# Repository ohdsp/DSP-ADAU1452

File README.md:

# [Open Hardware DSP Platform](http://www.ohdsp.org)
## ADAU145x DSP supporting ADAU1452, ADAU1451, and ADAU1450 devices
### Revision 2.1 - KiCad 9.0.4 update only - No Schematic/PCB changes
###### DSP-ADAU1452
---
# README
### Disclaimer
Copyright Paul Janicki 2025

Licensed under the TAPR Open Hardware License (www.tapr.org/OHL)

This documentation is distributed WITHOUT ANY EXPRESS OR IMPLIED WARRANTY, INCLUDING OF MERCHANTABILITY, SATISFACTORY QUALITY AND FITNESS FOR A PARTICULAR PURPOSE.

### What is this repository for?

**Quick summary**

This is a simple self-bootable ADAU1450, ADAU1451, or ADAU1452 based DSP board with 4 I2S (TDM/left and right justified and more) input and 4 output connectors. When used with the ADAU1451 and ADAU1452 parts there are also optical and coaxial SPDIF input and output connectors. 

There is an I2C/SPI connector for connection to the Analog Devices SigmaStudio USBi to EZ-Board Adapter (ADZS-USBI2EZB) or anything that will do the same job (eg freeUSBi). The board also features master and slave SPI connectors for use with other OHDSP boards. The board has space for a self-boot EEPROM and so with the ADZS-USBI2EZB or compatible device the board can be programmed as you wish and will selfboot the last program written when enabled. 

This board forms the core of the open hardware DSP platform which is designed to be a highly customisable and flexible DSP platform. 

This repository contains the KiCad design files, manufacturing Gerber/drill files, and PDF/drawing files for this board.

### What is the project folder structure?
Most folder names are self explanatory. Starting from the top level: \
*DSP-ADAU1452*
+ *Bill of Materials*  - This contains the bill of materials in CVS, LibreOffice Calc and XML formats
+ *Drawings*
    + *PCB* - This contains SVG and PDF outputs of PCB copper layers and assembly drawings
    + *Schematics* - This contains the PDF schematic drawing
+ *Gerbers* - This contains the PCB Gerbers and drill drawings for manufacture, there is also a zip file ready to send to most manufacturers
+ *KiCad* - This contains the original KiCad schematic and PCB design files

### How do I get set up?

**Summary of set up**

1. Set your self up a directory on a local disk, something simple will make life easier (eg C:\Electronics on Windows as used here), but anywhere will do just fine.
2. Download the Kicad-Libs from [https://github.com/ohdsp/KiCad-Libs](https://github.com/ohdsp/KiCad-Libs) and place in C:\Electronics\Kicad-Libs (or your chosen folder) 
3. Create a OHDSP subdirectory in C:\Electronics (so C:\Electronics\OHDSP)
3. Download this project to C:\Electronics\OHDSP\DSP-ADAU1452
4. Fire up Kicad
5. Open the main project file C:\Electronics\OHDSP\DSP-ADAU1452\KiCad\DSP-ADAU1452.pro
6. (Optional) Setup Pcbnew component library as below.
7. Do as you wish with the project, just keep it under the TAPR Open Hardware License.

Make sure your git setup doesn't exclude files used in the project (like .LIB files) or things may go wrong down the line.

**KiCad Library Configuration**

Note that you need to setup a Pcbnew library, but the eeschema libraries should work without any changes if you followed the instructions above.

To setup Pcbnew libraries:

In Pcbnew go to Preferences -> Footprint Libraries Manager. Under Global Libraries tab in the top list check if there is a nickname "MyKiCadLibs-Footprints" (usually at the end of the list). If there is but it points to the wrong place then change the Library Path to point to MyKiCadLibs-Footprints (eg C:\Electronics\KiCad-Libs\MyKiCadLibs-Footprints.pretty) folder for your setup. If this is missing you can use "Append with Wizard", choose "Files on my computer", click next, browse to library location (eg C:\Electronics\KiCad-Libs\MyKiCadLibs-Footprints.pretty) and select the folder MyKiCadLibs-Footprints.pretty, click next, check the Status column states OK and the Format is KiCad (if not re-download the library) and click next, then select "To global library configuration..." and click Finish.

To setup eeschema component libraries:
Either from KiCad project window go to Tools -> Run Library Editor OR under eeschema, go to Tools -> Library Editor. Then Preferences -> Component Libraries.

The top section "Component Library Files" should ideally contain only two libraries, the "power" library that ships with KiCad and "MyKiCadLibs-Lib" available from above. To setup MyKiCadLibs-Lib as a relative path under the "User defined search path" click add. Browse to the location of KiCad-Libs you download above (eg C:\Electronics\KiCad-Libs) and click "Select Folder". Say yes to add a relative path. Under component library files click add, browse to the KiCad-libs again (eg C:\Electronics\KiCad-Libs), select file "MyKiCadLibs-Lib.lib" and click open. MyKiCadLibs-lib should appear in the component library list with no path as it will be using the user defined search path set in the box below.

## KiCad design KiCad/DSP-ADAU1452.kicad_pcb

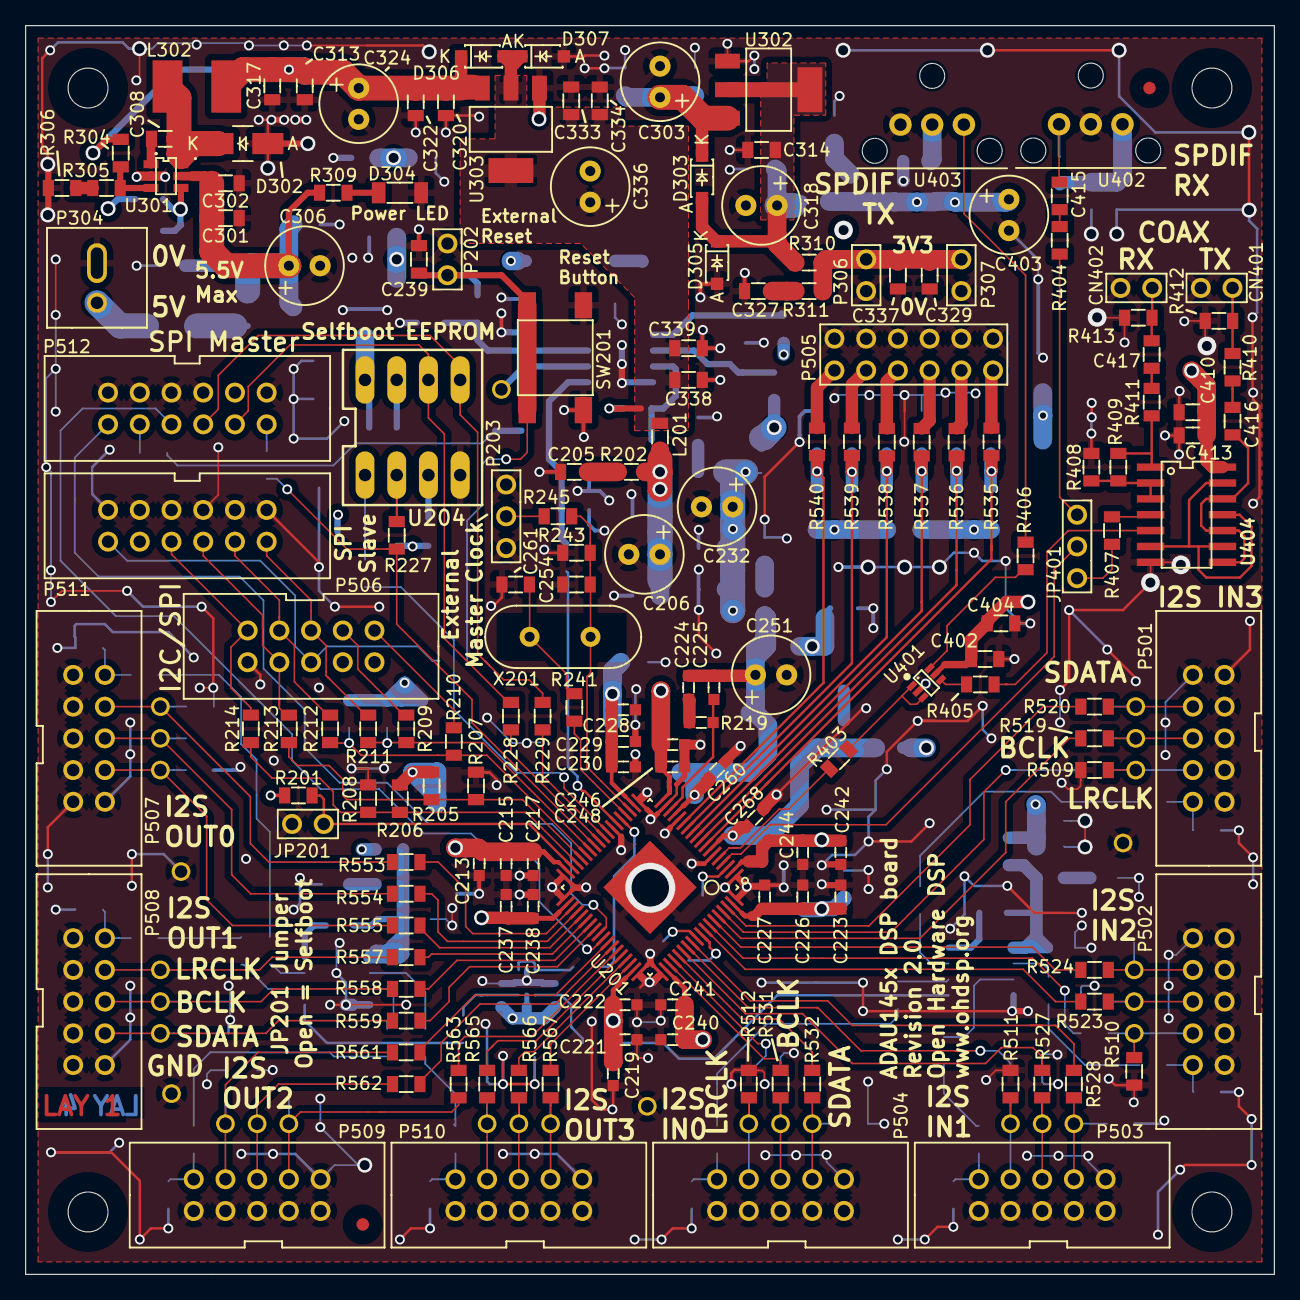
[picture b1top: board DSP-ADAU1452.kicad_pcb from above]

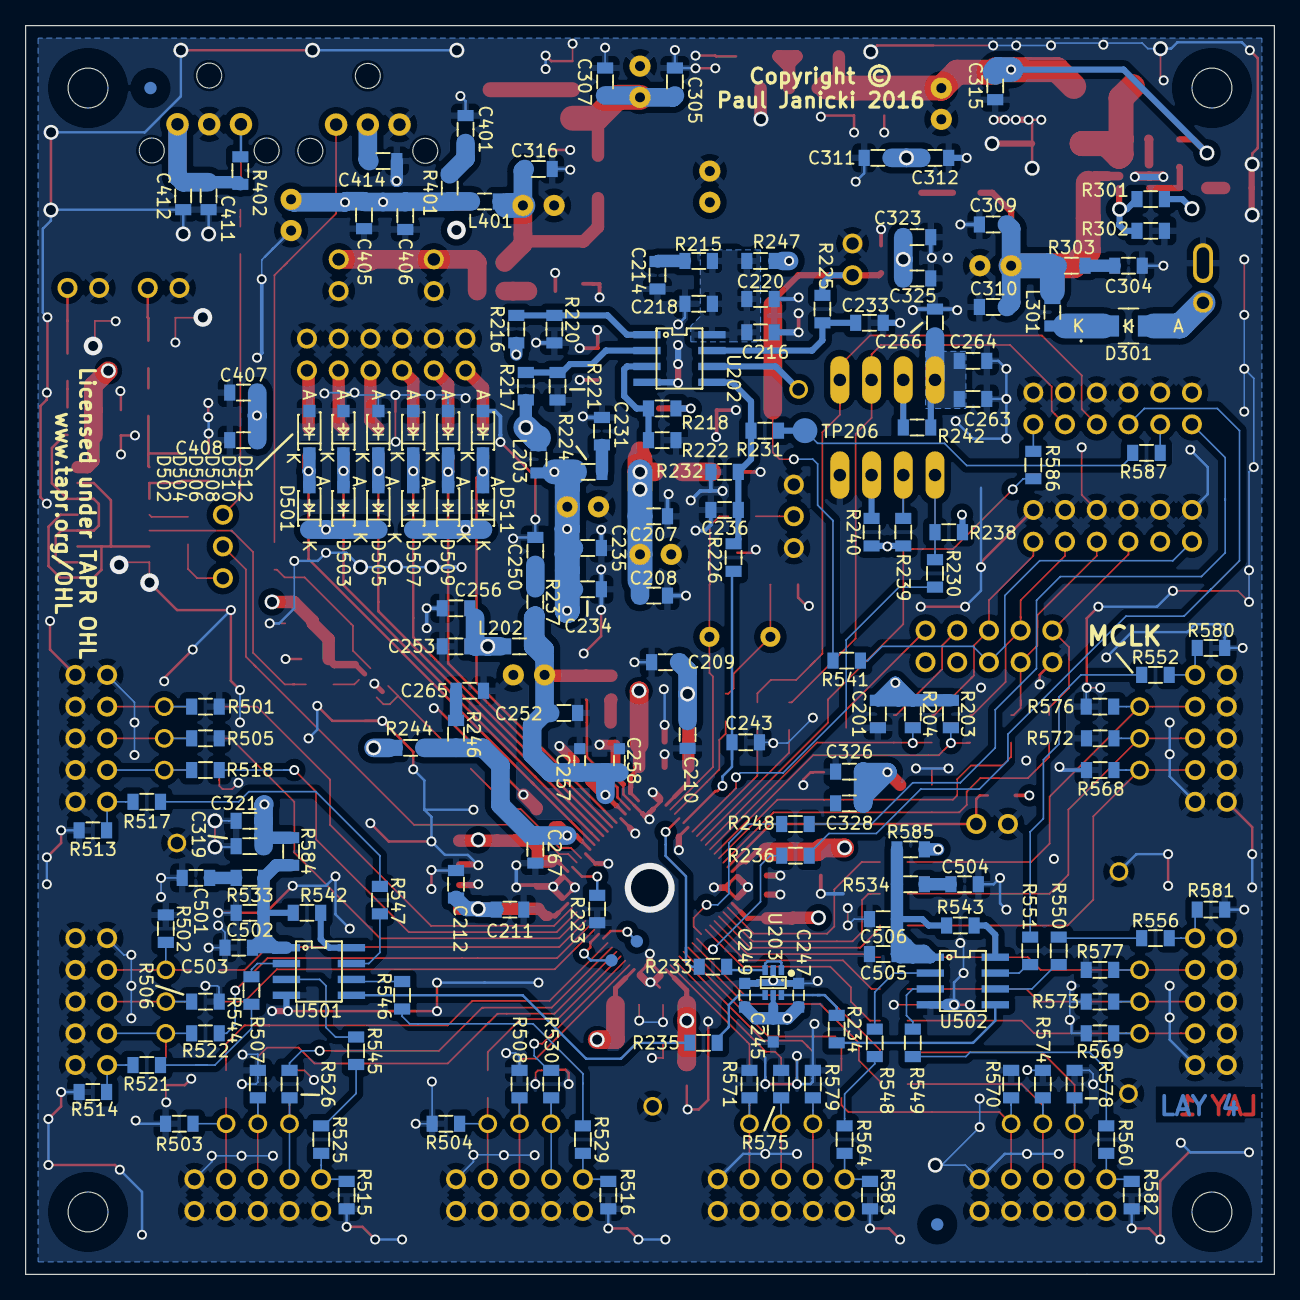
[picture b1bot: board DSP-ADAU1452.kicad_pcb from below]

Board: 4 copper layers, 100.0 x 100.0 mm, 377 parts (177 on the bottom side), 190 nets.

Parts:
C201, C208, C210, C212, C218, C233, C235, C236, C239, C243, C253, C264, C302, C307, C310, C314, C317, C319, C320, C323, C326, C329, C333, C338, C402, C406, C412, C413, C414, C416, C417, C503, C506: 100n; SMD-0805
C205, C214, C231, C250, C265, C304, C327, C401, C501, C504: 100p; SMD-0805
C206, C232, C251, C303, C306, C318, C324, C336, C403: 220u; CAP-TH-D6.3mmP2.5mm
C207, C234, C252, C267, C301, C305, C309, C313, C315, C316, C322, C334, C405, C502, C505: 22u; SMD-0805
C209, C211, C216, C256, C266, C321, C325, C328, C337, C339, C404, C410, C411: 10u; SMD-0805
C213, C219, C223, C228, C237, C240, C242, C245, C246, C257: 1u; SMD-0603
C215, C221, C226, C229, C238, C241, C244, C247, C248, C258, C268: 100n; SMD-0603
C217, C222, C227, C230, C249, C260: 10n; SMD-0603
C220, C263, C308, C415: 10n; SMD-0805
C224: 5n6; SMD-0603
C225: 150p; SMD-0603
C254, C261: 33p; SMD-0805
C311, C312, C407, C408: N/F; SMD-0805
CN401, CN402: COAX; CONN_SIL_2_1MM
D301, D302: B240A; DIODE-SMA
D303, D305, D306, D307, D501, D502, D503, D504, D505, D506, D507, D508, D509, D510, D511, D512: SS14L; DIODE-SOD-123
D304: Green LED 1206; SMD-1206
FID1, FID2, FID3, FID4: MNT_HOLE; FID-1MM-3MM
JP201: CONN_2x1; CONN_SIL_2_1MM
JP401: CONN_3x1; CONN_SIL_3_1MM
L201, L202, L203, L301, L401: 600R@100MHz; SMD-0805
L302: TYS50404R7N-10; IND-TYS5040-HS
MNT301, MNT302, MNT303, MNT304: MNT_HOLE; MNT_HOLE_3.2mm
P202, P306, P307: CONN_2x1; CONN_SIL_2_1MM
P203: CONN_3x1; CONN_SIL_3_1MM
P304: CONN_2x1; CONN-2WAY-2.54mm-3.81mm-SPACING
P501, P502, P503, P504, P506, P507, P508, P509, P510: CONN_02X05; CONN_DIL_2X5_BOX_1MM
P505: CONN_02X06; CONN_DIL_2X6_1MM
P511, P512: CONN_02X06; CONN_DIL_2X6_BOX_1MM
R201, R225, R542, R543: 1k; SMD-0805
R202, R215, R224, R237, R246, R303, R311, R401, R533, R534: 47; SMD-0805
R203, R204, R205, R206, R207, R208, R209, R210, R220, R239, R243, R245, R501, R502, R503, R504, R505, R506, R507, R508, R509, R510, R511, R512, R513, R514, R515, R516, R568, R569, R570, R571, R572, R573, R574, R575, R576, R577, R578, R579, R580, R581, R582, R583: N/F; SMD-0805
R211, R227, R228, R229, R230, R233, R234, R235, R236, R248, R403, R404, R405, R406, R407, R413, R544, R545, R546, R547, R548, R549, R550, R551, R553, R554, R555, R557, R558, R559, R561, R562, R563, R565, R566, R567: 75; SMD-0805
R212, R213, R214, R216, R223, R306, R517, R518, R519, R520, R521, R522, R523, R524, R525, R526, R527, R528, R529, R530, R531, R532, R541, R552, R556, R560, R564, R586, R587: 0; SMD-0805
R217: 12k; SMD-0805
R218: 3k3; SMD-0805
R219: 4k3; SMD-0603
R221: 3k; SMD-0805
R222: 3k6; SMD-0805
R226, R231, R241, R411: 100; SMD-0805
R232: 100k; SMD-0805
R238, R240, R242, R302, R402, R408, R409: 10k; SMD-0805
R244, R247, R310, R584, R585: 1; SMD-0805
R301: 16k; SMD-0805
R304: 24k; SMD-0805
R305: 15k; SMD-0805
R309: 470; SMD-0805
R410: 360; SMD-0805
R412: 91; SMD-0805
R535, R536, R537, R538, R539, R540: 4k7; SMD-0805
SW201: SWITCH; SW_TACT_SMD
TP201, TP501, TP502, TP503, TP504, TP505, TP506, TP507, TP508, TP509, TP510, TP511, TP512, TP513, TP514, TP515, TP516, TP517, TP518, TP519, TP520, TP521, TP522, TP523, TP524, TP525, TP526, TP527, TP528: PIN; TP-TH-1mm
TP204, TP205: PIN; TP-1mm
TP206: PIN; TP-2mm
U201: ADAU1452WBCPZ; IC-LFCSP72-HANDFIT
U202: ADM13307-5ARZ; IC_SOIC_8
U203: NC7WZ17P6X; IC-SC70-6
U204: 25AA1024; IC_DIP_8
U301: ADP2301AUJZ; IC-SOT23-6
U302: TLV1117LV33DCY; IC-SOT-223
U303: TLV1117LV12DCY; IC-SOT-223
U401: NC7WZ16P6X; IC-SC70-6
U402: IC-SPDIF-RX-OPTO; IC_SPDIF_OPTO
U403: IC-SPDIF-TX-OPTO; IC_SPDIF_OPTO
U404: 74HC04; IC_SOIC_14
U501, U502: NB3L553; IC_SOIC_8
X201: 24M576; XTAL_HC49_TH

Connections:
/ADAU1452/ADAU_SPDIF_RX: JP401.2, U201.4
/ADAU1452/ADAU_SPDIF_TX: R403.2, U201.5
/ADAU1452/ADCIN_BCLK0: R531.2, U201.57
/ADAU1452/ADCIN_BCLK1: R527.2, U201.60
/ADAU1452/ADCIN_BCLK2: R523.2, U201.65
/ADAU1452/ADCIN_BCLK3: R519.2, U201.68
/ADAU1452/ADCIN_LRCLK0: R530.2, U201.58
/ADAU1452/ADCIN_LRCLK1: R526.2, U201.61
/ADAU1452/ADCIN_LRCLK2: R522.2, U201.66
/ADAU1452/ADCIN_LRCLK3: R518.2, U201.69
/ADAU1452/ADCIN_SDATA0: R532.2, U201.59
/ADAU1452/ADCIN_SDATA1: R528.2, U201.62
/ADAU1452/ADCIN_SDATA2: R524.2, U201.67
/ADAU1452/ADCIN_SDATA3: R520.2, U201.70
/ADAU1452/AVDD: C267.1, C268.1, R244.1, R246.1, U201.7
/ADAU1452/DACOUT_BCLK0: R554.1, U201.40
/ADAU1452/DACOUT_BCLK1: R558.1, U201.43
/ADAU1452/DACOUT_BCLK2: R562.1, U201.48
/ADAU1452/DACOUT_BCLK3: R566.1, U201.51
/ADAU1452/DACOUT_LRCLK0: R553.1, U201.39
/ADAU1452/DACOUT_LRCLK1: R557.1, U201.42
/ADAU1452/DACOUT_LRCLK2: R561.1, U201.47
/ADAU1452/DACOUT_LRCLK3: R565.1, U201.50
/ADAU1452/DACOUT_SDATA0: R555.1, U201.41
/ADAU1452/DACOUT_SDATA1: R559.1, U201.44
/ADAU1452/DACOUT_SDATA2: R563.1, U201.49
/ADAU1452/DACOUT_SDATA3: R567.1, U201.52
/ADAU1452/DSP_RESET: C243.1, R226.1, U201.24
/ADAU1452/DVDD: C206.1, C207.1, C208.1, C209.1, C210.1, C211.1, C212.1, C213.1, C215.1, C217.1, C219.1, C221.1, C222.1, C223.1, C226.1, C227.1, C228.1, C229.1, C230.1, L201.2, R202.1, U201.20, U201.35, U201.53, U201.71
/ADAU1452/GLB_RESET: R231.1, R587.2, TP206.1
/ADAU1452/I2C_SCL: P506.1, R210.1
/ADAU1452/I2C_SDA: P506.3, R209.1
/ADAU1452/IOVDD: C232.1, C234.1, C235.1, C237.1, C238.1, C240.1, C241.1, C242.1, C244.1, C245.1, C246.1, C247.1, C248.1, C249.1, L203.2, R224.1, U201.2, U201.18, U201.38, U201.56, U203.5
/ADAU1452/MAN_RST_IN: C239.1, P202.1, R225.2, R541.2, SW201.1
/ADAU1452/MCLK: R235.1, U501.5
/ADAU1452/MCLK2: R234.1, U502.5
/ADAU1452/MCLK_ADAU: R233.2, U201.23
/ADAU1452/MISO/SDA: R204.2, R209.2, R211.2, U201.30
/ADAU1452/MOSI/ADDR1: R205.2, R207.2, R213.2, U201.32
/ADAU1452/M_SS: R230.2, R238.2, U204.1
/ADAU1452/PVDD: C224.1, C225.1, C251.1, C252.1, C257.1, C258.1, C260.1, L202.2, R237.1, U201.15
/ADAU1452/SCLK/SCL: R203.2, R210.2, R212.2, U201.31
/ADAU1452/SELFBOOT: JP201.1, R201.2, U201.34
/ADAU1452/SPI_MISO: P506.5, P511.2, R211.1
/ADAU1452/SPI_MOSI: P506.8, P511.6, R213.1
/ADAU1452/SPI_SCLK: P506.7, P511.4, R212.1
/ADAU1452/SPI_SS: P506.9, P511.8, R214.1
/ADAU1452/SS/ADDR0: R206.2, R208.2, R214.2, U201.33
/ADAU1452/XTALIN: C254.1, R243.1, R245.1, U201.21, X201.1
/ADAU1452/XTALOUT: R241.1, U201.22
/Connectors/AUXADCIN_1: D501.1, D502.2, R535.2, U201.8
/Connectors/AUXADCIN_2: D503.1, D504.2, R536.2, U201.9
/Connectors/AUXADCIN_3: D505.1, D506.2, R537.2, U201.10
/Connectors/AUXADCIN_4: D507.1, D508.2, R538.2, U201.11
/Connectors/AUXADCIN_5: D509.1, D510.2, R539.2, U201.12
/Connectors/AUXADCIN_6: D511.1, D512.2, R540.2, U201.13
/Connectors/I2C_RST: P506.6, P511.12, R541.1
/Connectors/MCLKA1: R529.2, R546.1
/Connectors/MCLKA2: R525.2, R545.1
/Connectors/MCLKA3: R521.2, R544.1
/Connectors/MCLKA4: R517.2, R547.1
/Connectors/MCLKB1: R551.1, R552.1
/Connectors/MCLKB2: R550.1, R556.1
/Connectors/MCLKB3: R549.1, R560.1
/Connectors/MCLKB4: R548.1, R564.1
/Connectors/M_MUTE: P512.12, R248.2
/Connectors/M_SPI_MISO: R227.1, R586.2, U201.29
/Connectors/M_SPI_MOSI: P512.6, R229.2, U204.5
/Connectors/M_SPI_SCLK: P512.4, R228.2, U204.6
/Connectors/M_SPI_SS: P512.8, R236.2
/Power Supply/2V1: C313.1, C315.1, C317.1, C320.1, C322.1, C324.1, D306.2, L302.2, R304.2, U303.3
GNDD: C201.2, C205.2, C206.2, C207.2, C208.2, C209.2, C210.2, C211.2, C212.2, C213.2, C214.2, C215.2, C216.2, C217.2, C218.2, C219.2, C220.2, C221.2, C222.2, C223.2, C226.2, C227.2, C228.2, C229.2, C230.2, C231.2, C232.2, C233.2, C234.2, C235.2, C236.2, C237.2, C238.2, C239.2, C240.2, C241.2, C242.2, C243.2, C244.2, C245.2, C246.2, C247.2, C248.2, C249.2, C250.2, C251.2, C252.2, C253.2, C254.2, C256.2, C257.2, C258.2, C260.2, C261.2, C263.2, C264.2, C265.2, C266.2, C267.2, C268.2, C301.1, C302.1, C303.2, C304.2, C305.2, C306.2, C307.2, C309.1, C310.1, C311.1, C312.1, C313.2, C314.2, C315.2, C316.2, C317.2, C318.2, C319.2, C320.2, C321.2, C322.2, C323.2, C324.2, C325.2, C326.2, C327.2, C328.2, C329.2, C333.2, C334.2, C336.2, C337.2, C338.2, C339.2, C401.2, C402.2, C403.2, C404.2, C405.2, C406.2, C407.2, C408.2, C410.2, C411.2, C412.2, C413.2, C414.2, C501.2, C502.2, C503.2, C504.2, C505.2, C506.2, CN401.2, CN402.2, D302.1, D304.2, D305.1, D307.1, D502.1, D504.1, D506.1, D508.1, D510.1, D512.1, JP201.2, P202.2, P203.1, P203.3, P304.2, P306.2, P307.2, P501.1, P501.3, P501.5, P501.7, P501.9, P501.10, P502.1, P502.3, P502.5, P502.7, P502.9, P502.10, P503.1, P503.3, P503.5, P503.7, P503.9, P503.10, P504.1, P504.3, P504.5, P504.7, P504.9, P504.10, P505.1, P505.3, P505.5, P505.7, P505.9, P505.11, P506.10, P507.1, P507.3, P507.5, P507.7, P507.9, P507.10, P508.1, P508.3, P508.5, P508.7, P508.9, P508.10, P509.1, P509.3, P509.5, P509.7, P509.9, P509.10, P510.1, P510.3, P510.5, P510.7, P510.9, P510.10, P511.1, P511.3, P511.5, P511.7, P511.9, P511.11, P512.1, P512.3, P512.5, P512.7, P512.9, P512.11, R207.1, R208.1, R220.1, R221.1, R222.1, R223.1, R232.1, R243.2, R302.1, R306.1, R408.1, R412.1, R413.1, R501.1, R502.1, R503.1, R504.1, R505.1, R506.1, R507.1, R508.1, R509.1, R510.1, R511.1, R512.1, R513.1, R514.1, R515.1, R516.1, R568.1, R569.1, R570.1, R571.1, R572.1, R573.1, R574.1, R575.1, R576.1, R577.1, R578.1, R579.1, R580.1, R581.1, R582.1, R583.1, SW201.2, TP513.1, TP514.1, TP515.1, TP516.1, U201.1, U201.6, U201.14, U201.17, U201.19, U201.25, U201.36, U201.37, U201.54, U201.55, U201.72, U201.EP1, U202.4, U203.2, U204.4, U301.2, U302.1, U303.1, U401.2, U402.2, U403.3, U404.7, U501.4, U502.4
unnamed: C205.1, R202.2
unnamed: C214.1, R215.2
unnamed: C216.1, C218.1, C220.1, R215.1, R247.1, U202.8
unnamed: C224.2, R219.1
unnamed: C225.2, R219.2, U201.16
unnamed: C231.1, R224.2
unnamed: C233.1, R225.1, U202.7
unnamed: C236.1, R226.2, R231.2, R232.2, U202.5
unnamed: C250.1, R237.2
unnamed: C261.1, R241.2, X201.2
unnamed: C265.1, R246.2
unnamed: C304.1, R303.2
unnamed: C308.1, U301.1
unnamed: C308.2, D302.2, L302.1, U301.6
unnamed: C327.1, R311.2
unnamed: C329.1, C337.1, P306.1, P307.1, R310.1, R311.1
unnamed: C401.1, R401.2
unnamed: C402.1, C403.1, C404.1, C405.1, C406.1, C407.1, C408.1, C410.1, C411.1, C412.1, C413.1, C414.1, L401.2, R401.1, R402.1, U401.5, U402.1, U403.2, U404.14
unnamed: C415.1, R404.2
unnamed: C415.2, R402.2, U402.3
unnamed: C416.1, R410.2
unnamed: C416.2, U404.8, U404.10, U404.12
unnamed: C417.1, R411.2
unnamed: C417.2, CN402.1, R413.2
unnamed: C501.1, R533.2
unnamed: C502.1, C503.1, R533.1, R542.2, R584.2, U501.1
unnamed: C504.1, R534.2
unnamed: C505.1, C506.1, R534.1, R543.2, R585.2, U502.1
unnamed: CN401.1, R410.1, R412.2
unnamed: D301.1, P304.1
unnamed: D301.2, L301.1
unnamed: D304.1, R309.2
unnamed: JP401.1, R404.1
unnamed: JP401.3, R407.2
unnamed: P203.2, R245.2
unnamed: P501.2, R513.2, R517.1
unnamed: P501.4, R509.2, R518.1, TP501.1
unnamed: P501.6, R505.2, R519.1, TP505.1
unnamed: P501.8, R501.2, R520.1, TP506.1
unnamed: P502.2, R514.2, R521.1
unnamed: P502.4, R510.2, R522.1, TP502.1
unnamed: P502.6, R506.2, R523.1, TP507.1
unnamed: P502.8, R502.2, R524.1, TP508.1
unnamed: P503.2, R515.2, R525.1
unnamed: P503.4, R511.2, R526.1, TP503.1
unnamed: P503.6, R507.2, R527.1, TP509.1
unnamed: P503.8, R503.2, R528.1, TP510.1
unnamed: P504.2, R516.2, R529.1
unnamed: P504.4, R512.2, R530.1, TP504.1
unnamed: P504.6, R508.2, R531.1, TP511.1
unnamed: P504.8, R504.2, R532.1, TP512.1
unnamed: P505.2, R535.1
unnamed: P505.4, R536.1
unnamed: P505.6, R537.1
unnamed: P505.8, R538.1
unnamed: P505.10, R539.1
unnamed: P505.12, R540.1
unnamed: P507.2, R552.2, R580.2
unnamed: P507.4, R553.2, R576.2, TP517.1
unnamed: P507.6, R554.2, R572.2, TP521.1
unnamed: P507.8, R555.2, R568.2, TP522.1
unnamed: P508.2, R556.2, R581.2
unnamed: P508.4, R557.2, R577.2, TP518.1
unnamed: P508.6, R558.2, R573.2, TP523.1
unnamed: P508.8, R559.2, R569.2, TP524.1
unnamed: P509.2, R560.2, R582.2
unnamed: P509.4, R561.2, R578.2, TP519.1
unnamed: P509.6, R562.2, R574.2, TP525.1
unnamed: P509.8, R563.2, R570.2, TP526.1
unnamed: P510.2, R564.2, R583.2
unnamed: P510.4, R565.2, R579.2, TP520.1
unnamed: P510.6, R566.2, R575.2, TP527.1
unnamed: P510.8, R567.2, R571.2, TP528.1
unnamed: P512.2, R586.1
unnamed: P512.10, R587.1
unnamed: R216.2, R220.2, U202.1
unnamed: R217.2, R221.2, U202.2
unnamed: R218.2, R222.2, U202.3
unnamed: R223.2, U201.3
unnamed: R227.2, R239.2, U204.2
unnamed: R228.1, U201.28
unnamed: R229.1, U201.27
unnamed: R230.1, U201.26
unnamed: R233.1, U203.1, U203.3
unnamed: R234.2, U203.6
unnamed: R235.2, U203.4
unnamed: R236.1, U201.46
unnamed: R240.2, U204.3
unnamed: R242.2, U204.7
unnamed: R248.1, U201.45
unnamed: R301.1, R302.2, U301.4
unnamed: R304.1, R305.2, U301.3
unnamed: R305.1, R306.2
unnamed: R403.1, U401.1, U401.3
unnamed: R405.1, U404.5
unnamed: R405.2, U401.4
unnamed: R406.1, U401.6
unnamed: R406.2, U403.1
unnamed: R407.1, U404.4
unnamed: R408.2, R409.1, U404.2, U404.3
unnamed: R409.2, R411.1, U404.1
unnamed: R542.1, U501.8
unnamed: R543.1, U502.8
unnamed: R544.2, U501.2
unnamed: R545.2, U501.3
unnamed: R546.2, U501.6
unnamed: R547.2, U501.7
unnamed: R548.2, U502.2
unnamed: R549.2, U502.3
unnamed: R550.2, U502.6
unnamed: R551.2, U502.7
unnamed: TP201.1, U202.6
unnamed: TP204.1, U201.64
unnamed: TP205.1, U201.63
unnamed: U404.6, U404.9, U404.11, U404.13
VAA: C201.1, C253.1, C256.1, C263.1, C264.1, C266.1, C314.1, C316.1, C318.1, C319.1, C321.1, C323.1, C325.1, C326.1, C328.1, D303.1, D305.2, D501.2, D503.2, D505.2, D507.2, D509.2, D511.2, L202.1, L203.1, L401.1, R201.1, R203.1, R204.1, R205.1, R206.1, R216.1, R217.1, R238.1, R239.1, R240.1, R242.1, R244.2, R247.2, R301.2, R310.2, R584.1, R585.1, U204.8, U302.2
VCC: C301.2, C302.2, C303.1, C305.1, C306.1, C307.1, C309.2, C310.2, C311.2, C312.2, D303.2, L301.2, R303.1, R309.1, U301.5, U302.3
VDD: C333.1, C334.1, C336.1, C338.1, C339.1, D306.1, D307.2, L201.1, R218.1, U303.2

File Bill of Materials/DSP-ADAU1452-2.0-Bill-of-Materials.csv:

Reference; Quantity; Footprint; Value; Description; Voltage; Type; Tolerance; Size; Current; Power; 
C205 C214 C231 C250 C265 C304 C327 C401 C501 C504 ;10;SMD-0805;100p;'Ceramic capacitor;'50V;'C0G;'5%;'0805;';';
C206 C232 C251 C318 C324 C336 C403 ;7;CAP-TH-D6.3mmP2.5mm;220u;'Low impedance aluminium electrolytic capacitor - Panasonic FC, FR or similar;'10V;'2.5mm pitch, 6.3mm diameter;';';';';
C207 C234 C267 C313 C315 C316 C322 C334 C405 C502 C505 ;11;SMD-0805;22u;'Ceramic capacitor;'10V;'X5R;'20%;'0805;';';
C201 C208 C210 C212 C218 C233 C235 C236 C239 C243 C253 C264 C302 C307 C310 C314 C317 C319 C320 C323 C326 C329 C333 C338 C402 C406 C412 C413 C414 C416 C417 C503 C506 ;33;SMD-0805;100n;'Ceramic capacitor;'50V;'X7R;'10%;'0805;';';
C209 C211 C216 C256 C266 C321 C325 C328 C337 C339 C404 C410 C411 ;13;SMD-0805;10u;'Ceramic capacitor;'10V;'X5R;'20%;'0805;';';
C213 C219 C223 C228 C237 C240 C242 C245 C246 C257 ;10;SMD-0603;1u;'Ceramic capacitor;'10V;'X7R;'10%;'0603;';';
C215 C221 C226 C229 C238 C241 C244 C247 C248 C258 C268 ;11;SMD-0603;100n;'Ceramic capacitor;'50V;'X7R;'10%;'0603;';';
C217 C222 C227 C230 C249 C260 ;6;SMD-0603;10n;'Ceramic capacitor;'50V;'X7R;'10%;'0603;';';
C224 ;1;SMD-0603;5n6;'Ceramic capacitor;'50V;'X7R;'10%;'0603;';';
C225 ;1;SMD-0603;150p;'Ceramic capacitor;'50V;'C0G;'5%;'0603;';';
C252 ;1;SMD-0805;22u;'Ceramic capacitor;'10V;'X5R;'20%;';';';
C254 C261 ;2;SMD-0805;33p;'Ceramic capacitor;'50V;'C0G;'5%;'0805;';';
C220 C263 C308 C415 ;4;SMD-0805;10n;'Ceramic capacitor;'50V;'X7R;'10%;'0805;';';
C303 C306 ;2;CAP-TH-D6.3mmP2.5mm;220u;'Aluminium electrolytic capacitor;'16V;'2.5mm pitch, 6.3mm diameter;';';';';
C301 C305 C309 ;3;SMD-0805;22u;'Ceramic capacitor;'25V;'X5R;'20%;'0805;';';
C311 C312 ;2;SMD-0805;N/F;'Ceramic capacitor;'16V;'X7R;'10%;'0805;';';
C407 C408 ;2;SMD-0805;N/F;'Ceramic capacitor;'10V;'X7R;'10%;'0805;';';
CN401 CN402 ;2;CONN_SIL_2_1MM;COAX;'1x2 2.54mm pitch pin header - use with 75Ohm coax;';';';';';';
D301 D302 ;2;DIODE-SMA;B240A;'B240A 2A 40V Schottky Rectifier - SMA (DO-214AC);';';';';';';
D303 D305 D306 D307 D501 D502 D503 D504 D505 D506 D507 D508 D509 D510 D511 D512 ;16;DIODE-SOD-123;SS14L;'SS14L 1A 40V Schottky rectifier - Sub-SMA (SOD-123);';';';';';';
D304 ;1;SMD-1206;Green LED 1206;'Green LED - SMD - Vf 1.8V to 2.2V;';';';'1206;';';
FID1 FID2 FID3 FID4 ;4;FID-1MM-3MM;MNT_HOLE;'Fiducial;';';';';';';
L201 L202 L203 L301 L401 ;5;SMD-0805;600R@100MHz;'Ferrite bead, current rating 1A or higher, 600R@100MHz;';';';'0805;'=>1A;';
L302 ;1;IND-TYS5040-HS;TYS50404R7N-10;'Laird Technologies TYS5040 4.7uH Inductor - 3A Irms, 3.5A Isat, 0.030ohm, 28MHz;';';';';'3A;';
MNT301 MNT302 MNT303 MNT304 ;4;MNT_HOLE_3.2mm;MNT_HOLE;'Mounting hole;';';';';';';
JP201 P202 P306 P307 ;4;CONN_SIL_2_1MM;CONN_2x1;'1x2 2.54mm pitch pin header;';';';';';';
JP401 P203 ;2;CONN_SIL_3_1MM;CONN_3x1;'1x3 2.54mm pitch pin header;';';';';';';
P304 ;1;CONN-2WAY-2.54mm-3.81mm-SPACING;CONN_2x1;'2 way screw terminal, any 2.54mm to 3.81mm pitch part;';';';';';';
P501 P502 P503 P504 P506 P507 P508 P509 P510 ;9;CONN_DIL_2X5_BOX_1MM;CONN_02X05;'2x5 2.54mm pitch box header;';';';';';';
P505 ;1;CONN_DIL_2X6_1MM;CONN_02X06;'2x6 2.54mm pitch box header;';';';';';';
P511 P512 ;2;CONN_DIL_2X6_BOX_1MM;CONN_02X06;'2x6 2.54mm pitch box header;';';';';';';
R201 R225 R542 R543 ;4;SMD-0805;1k;'Thick or thin film resistor;';';'1%;'0805;';'100mW;
R202 R215 R224 R237 R246 R303 R311 R401 R533 R534 ;10;SMD-0805;47;'Thick or thin film resistor;';';'1%;'0805;';'100mW;
R203 R204 R205 R206 R207 R208 R209 R210 R220 R239 R243 R245 R501 R502 R503 R504 R505 R506 R507 R508 R509 R510 R511 R512 R513 R514 R515 R516 R568 R569 R570 R571 R572 R573 R574 R575 R576 R577 R578 R579 R580 R581 R582 R583 ;44;SMD-0805;N/F;'Thick or thin film resistor;';';'1%;'0805;';'100mW;
R211 R227 R228 R229 R230 R233 R234 R235 R236 R248 R403 R404 R405 R406 R407 R413 R544 R545 R546 R547 R548 R549 R550 R551 R553 R554 R555 R557 R558 R559 R561 R562 R563 R565 R566 R567 ;36;SMD-0805;75;'Thick or thin film resistor;';';'1%;'0805;';'100mW;
R217 ;1;SMD-0805;12k;'Thick or thin film resistor;';';'1%;'0805;';'100mW;
R218 ;1;SMD-0805;3k3;'Thick or thin film resistor;';';'1%;'0805;';'100mW;
R219 ;1;SMD-0603;4k3;'Thick or thin film resistor;';';'1%;'0603;';'63mW;
R221 ;1;SMD-0805;3k;'Thick or thin film resistor;';';'1%;'0805;';'100mW;
R222 ;1;SMD-0805;3k6;'Thick or thin film resistor;';';'1%;'0805;';'100mW;
R212 R213 R214 R216 R223 R306 R517 R518 R519 R520 R521 R522 R523 R524 R525 R526 R527 R528 R529 R530 R531 R532 R541 R552 R556 R560 R564 R586 R587 ;29;SMD-0805;0;'Thick or thin film resistor;';';'1%;'0805;';'100mW;
R226 R231 R241 R411 ;4;SMD-0805;100;'Thick or thin film resistor;';';'1%;'0805;';'100mW;
R232 ;1;SMD-0805;100k;'Thick or thin film resistor;';';'1%;'0805;';'100mW;
R238 R240 R242 R302 R402 R408 R409 ;7;SMD-0805;10k;'Thick or thin film resistor;';';'1%;'0805;';'100mW;
R244 R247 R310 R584 R585 ;5;SMD-0805;1;'Thick or thin film resistor;';';'1%;'0805;';'100mW;
R301 ;1;SMD-0805;16k;'Thick or thin film resistor;';';'1%;'0805;';'100mW;
R304 ;1;SMD-0805;24k;'Thick or thin film resistor;';';'1%;'0805;';'100mW;
R305 ;1;SMD-0805;15k;'Thick or thin film resistor;';';'1%;'0805;';'100mW;
R309 ;1;SMD-0805;470;'Thick or thin film resistor;';';'1%;'0805;';'100mW;
R410 ;1;SMD-0805;360;'Thick or thin film resistor;';';'1%;'0805;';'100mW;
R412 ;1;SMD-0805;91;'Thick or thin film resistor;';';'1%;'0805;';'100mW;
R535 R536 R537 R538 R539 R540 ;6;SMD-0805;4k7;'Thick or thin film resistor;';';'1%;'0805;';'100mW;
SW201 ;1;SW_TACT_SMD;SWITCH;'6mm x 6mm SMD tactile switch - e.g. TE FSM2JSMA;';';';';';';
TP201 TP501 TP502 TP503 TP504 TP505 TP506 TP507 TP508 TP509 TP510 TP511 TP512 TP513 TP514 TP515 TP516 TP517 TP518 TP519 TP520 TP521 TP522 TP523 TP524 TP525 TP526 TP527 TP528 ;29;TP-TH-1mm;PIN;Test Point (Through hole);;;;;;;
TP204 TP205 ;2;TP-1mm;PIN;Test Point (SMD);;;;;;;
TP206 ;1;TP-2mm;PIN;Test Point (SMD);;;;;;;
U201 ;1;IC-LFCSP72-HANDFIT;ADAU1452WBCPZ;'SigmaDSP Digital Audio Processor - Use ADAU1452, ADAU1451, or ADAU1450;';';';';';';
U202 ;1;IC_SOIC_8;ADM13307-5ARZ;'Triple Processor Supervisors - Use ADM13307-5ARZ only (Sense1 = 3v3, Sense2/3=Adj);';';';';';';
U203 ;1;IC-SC70-6;NC7WZ17P6X;'UHS Dual Buffer with Schmitt Trigger Inputs;';';';';';';
U204 ;1;IC_DIP_8;25AA1024;'1 Mbit SPI Bus Serial EEPROM - Fit 8 pin DIP socket;';';';';';';
U301 ;1;IC-SOT23-6;ADP2301AUJZ;'1.2 A, 20 V, 700 kHz/1.4 MHz, Nonsynchronous Step-Down Regulator;';';';';';';
U302 ;1;IC-SOT-223;TLV1117LV33DCY;'TLV1117LV 1-A, Positive Fixed-Voltage, Low-Dropout Regulator - Fixed 3V3;';';';';';';
U303 ;1;IC-SOT-223;TLV1117LV12DCY;'TLV1117LV 1-A, Positive Fixed-Voltage, Low-Dropout Regulator - Fixed 1V2;';';';';';';
U401 ;1;IC-SC70-6;NC7WZ16P6X;'UHS Dual Buffer;';';';';';';
U402 ;1;IC_SPDIF_OPTO;IC-SPDIF-RX-OPTO;'TOSLINK receiver e.g. CLIFF FC684205R;';';';';';';
U403 ;1;IC_SPDIF_OPTO;IC-SPDIF-TX-OPTO;'TOSLINK transmitter e.g. CLIFF FC684205T;';';';';';';
U404 ;1;IC_SOIC_14;74HC04;'74HC04 Hex Inverter - SOIC-14;';';';';';';
U501 U502 ;2;IC_SOIC_8;NB3L553;'On Semi - 1:4 Clock Fanout Buffer;';';';';';';
X201 ;1;XTAL_HC49_TH;24M576;'HC49 Crystal, 24.576MHz, 18pF;';';';';';';

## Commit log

2016-01-24 Release 1.0
    Release 1.0
2016-04-27 Updated readme with R308 issue (should be not fitted)
    Updated readme with R308 issue (should be not fitted)
2016-05-26 Revision 2.0
2016-07-01 Revision 2.0
    Minor readme website link update
2016-07-01 Revision 2.0
    Update BOM sheet name
2025-09-12 KiCad 9.04
    Updated to KiCad 9.04

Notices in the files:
KiCad/DSP-ADAU1452.kicad_pcb:
Licensed under TAPR OHL
Copyright ©
